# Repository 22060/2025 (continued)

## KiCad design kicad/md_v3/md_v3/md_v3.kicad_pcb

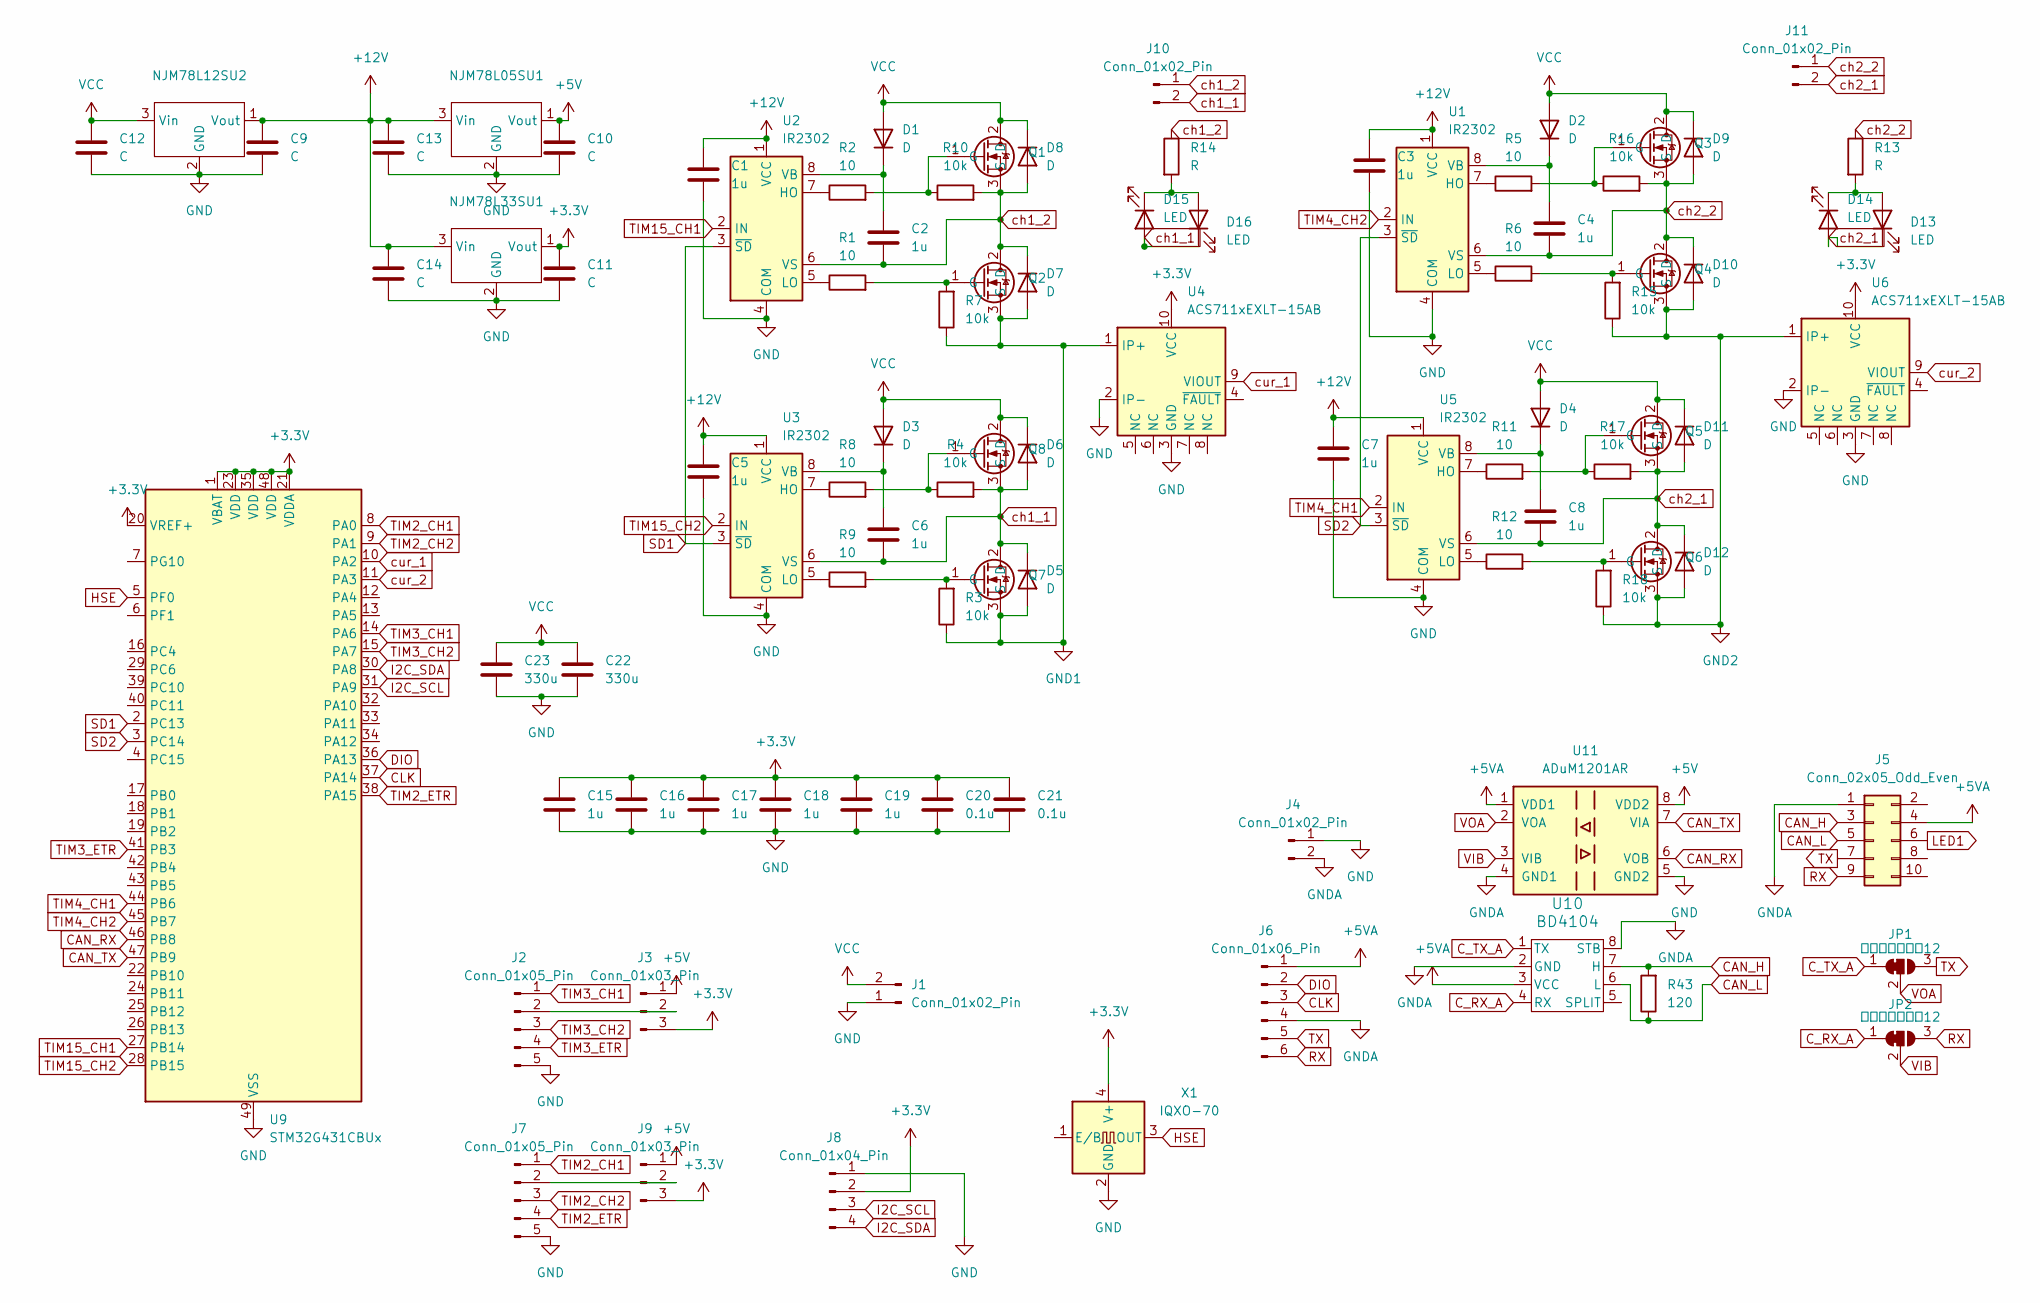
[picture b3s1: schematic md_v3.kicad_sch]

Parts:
C1, C2, C3, C4, C5, C6, C7, C8, C15, C16, C17, C18, C19: 1u; C_0603_1608Metric
C9, C10, C11, C12, C13, C14: C; C_0603_1608Metric
C20, C21: 0.1u; C_0603_1608Metric
C22, C23: 330u; C_Elec_10x10.2
D1, D2, D3, D4: D; D_MicroSMP_AK
D5, D6, D7, D8, D9, D10, D11, D12: D; D_SOD-323_HandSoldering
D13, D14, D15, D16: LED; LED_0603_1608Metric
J1: Conn_01x02_Pin; AMASS_XT30PW-M_1x02_P2.50mm_Horizontal
J2, J7: Conn_01x05_Pin; JST_XH_S5B-XH-A_1x05_P2.50mm_Horizontal
J3, J9: Conn_01x03_Pin; PinSocket_1x03_P2.54mm_Vertical
J4: Conn_01x02_Pin; PinHeader_1x02_P2.54mm_Vertical
J5: Conn_02x05_Odd_Even; PinHeader_2x05_P2.54mm_Horizontal
J6: Conn_01x06_Pin; JST_ZH_B6B-ZR_1x06_P1.50mm_Vertical
J8: Conn_01x04_Pin; PinSocket_1x04_P2.54mm_Vertical
J10, J11: Conn_01x02_Pin; AMASS_XT30PW-F_1x02_P2.50mm_Horizontal
JP1, JP2: ソルダジャンパ12; SolderJumper-3_P1.3mm_Bridged12_Pad1.0x1.5mm
NJM78L05SU1, NJM78L12SU2, NJM78L33SU1: SOT-89-3
Q1, Q2, Q3, Q4, Q5, Q6, Q7, Q8: RD3L07BBG
R1, R2, R5, R6, R8, R9, R11, R12: 10; R_0603_1608Metric_Pad0.98x0.95mm_HandSolder
R3, R4, R7, R10, R15, R16, R17, R18: 10k; R_0603_1608Metric_Pad0.98x0.95mm_HandSolder
R13, R14: R; R_0603_1608Metric_Pad0.98x0.95mm_HandSolder
R43: 120; R_0603_1608Metric_Pad0.98x0.95mm_HandSolder
U1, U2, U3, U5: IR2302; SOIC-8_3.9x4.9mm_P1.27mm
U4, U6: ACS711xEXLT-15AB; Allegro_QFN-12-10-1EP_3x3mm_P0.5mm
U9: STM32G431CBUx; QFN-48-1EP_7x7mm_P0.5mm_EP5.6x5.6mm
U10: BD4104; SOP-J8
U11: ADuM1201AR; SOIC-8_3.9x4.9mm_P1.27mm
X1: IQXO-70; Oscillator_SMD_IQD_IQXO70-4Pin_7.5x5.0mm

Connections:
+3.3V: C11.1, C15.1, C16.1, C17.1, C18.1, C19.1, C20.1, C21.1, J3.3, J8.2, J9.3, NJM78L33SU1.1 (Vout), U4.10 (VCC), U6.10 (VCC), U9.1 (VBAT), U9.20 (VREF+), U9.21 (VDDA), U9.23 (VDD), U9.35 (VDD), U9.48 (VDD), X1.4 (V+)
+5V: C10.1, J3.1, J9.1, NJM78L05SU1.1 (Vout), U11.8 (VDD2)
+5VA: J5.4, J6.1, U10.3 (VCC), U11.1 (VDD1)
+12V: C1.1, C3.1, C5.1, C7.1, C9.1, C13.1, C14.1, NJM78L05SU1.3 (Vin), NJM78L12SU2.1 (Vout), NJM78L33SU1.3 (Vin), U1.1 (VCC), U2.1 (VCC), U3.1 (VCC), U5.1 (VCC)
CAN_H: J5.3, R43.2, U10.7 (H)
CAN_L: J5.5, R43.1, U10.6 (L)
CAN_RX: U9.46 (PB8), U11.6 (VOB)
CAN_TX: U9.47 (PB9), U11.7 (VIA)
CLK: J6.3, U9.37 (PA14)
C_RX_A: JP2.1 (A), U10.4 (RX)
C_TX_A: JP1.1 (A), U10.1 (TX)
DIO: J6.2, U9.36 (PA13)
GND: C1.2, C3.2, C5.2, C7.2, C9.2, C10.2, C11.2, C12.2, C13.2, C14.2, C15.2, C16.2, C17.2, C18.2, C19.2, C20.2, C21.2, C22.2, C23.2, J1.1, J2.5, J4.1, J7.5, J8.1, NJM78L05SU1.2 (GND), NJM78L12SU2.2 (GND), NJM78L33SU1.2 (GND), U1.4 (COM), U2.4 (COM), U3.4 (COM), U4.2 (IP-), U4.3 (GND), U5.4 (COM), U6.2 (IP-), U6.3 (GND), U9.49 (VSS), U11.5 (GND2), X1.2 (GND)
GND1: D5.2 (A), D7.2 (A), Q2.3 (S), Q7.3 (S), R3.1, R7.1, U4.1 (IP+)
GND2: D10.2 (A), D12.2 (A), Q4.3 (S), Q6.3 (S), R15.1, R18.1, U6.1 (IP+)
GNDA: J4.2, J5.1, J6.4, U10.2 (GND), U10.8 (STB), U11.4 (GND1)
HSE: U9.5 (PF0), X1.3 (OUT)
I2C_SCL: J8.3, U9.31 (PA9)
I2C_SDA: J8.4, U9.30 (PA8)
LED1: J5.6
unnamed: C2.1, D1.1 (K), U2.8 (VB)
unnamed: C4.1, D2.1 (K), U1.8 (VB)
unnamed: C6.1, D3.1 (K), U3.8 (VB)
unnamed: C8.1, D4.1 (K), U5.8 (VB)
unnamed: D13.2 (A), D14.1 (K), R13.2
unnamed: D15.1 (K), D16.2 (A), R14.2
unnamed: J2.2, J3.2
unnamed: J7.2, J9.2
unnamed: Q1.1 (G), R2.2, R10.1
unnamed: Q2.1 (G), R1.2, R7.2
unnamed: Q3.1 (G), R5.2, R16.1
unnamed: Q4.1 (G), R6.2, R15.2
unnamed: Q5.1 (G), R11.2, R17.1
unnamed: Q6.1 (G), R12.2, R18.2
unnamed: Q7.1 (G), R3.2, R9.2
unnamed: Q8.1 (G), R4.1, R8.2
unnamed: R5.1, U1.7 (HO)
unnamed: R6.1, U1.5 (LO)
unnamed: R2.1, U2.7 (HO)
unnamed: R1.1, U2.5 (LO)
unnamed: R8.1, U3.7 (HO)
unnamed: R9.1, U3.5 (LO)
unnamed: R11.1, U5.7 (HO)
unnamed: R12.1, U5.5 (LO)
RX: J5.9, J6.6, JP2.3 (B)
SD1: U2.3 (~SD), U3.3 (~SD), U9.2 (PC13)
SD2: U1.3 (~SD), U5.3 (~SD), U9.3 (PC14)
TIM2_CH1: J7.1, U9.8 (PA0)
TIM2_CH2: J7.3, U9.9 (PA1)
TIM2_ETR: J7.4, U9.38 (PA15)
TIM3_CH1: J2.1, U9.14 (PA6)
TIM3_CH2: J2.3, U9.15 (PA7)
TIM3_ETR: J2.4, U9.41 (PB3)
TIM4_CH1: U5.2 (IN), U9.44 (PB6)
TIM4_CH2: U1.2 (IN), U9.45 (PB7)
TIM15_CH1: U2.2 (IN), U9.27 (PB14)
TIM15_CH2: U3.2 (IN), U9.28 (PB15)
TX: J5.7, J6.5, JP1.3 (B)
VCC: C12.1, C22.1, C23.1, D1.2 (A), D2.2 (A), D3.2 (A), D4.2 (A), D6.1 (K), D8.1 (K), D9.1 (K), D11.1 (K), J1.2, NJM78L12SU2.3 (Vin), Q1.2 (D), Q3.2 (D), Q5.2 (D), Q8.2 (D)
VIB: JP2.2 (C), U11.3 (VIB)
VOA: JP1.2 (C), U11.2 (VOA)
ch1_1: C6.2, D5.1 (K), D6.2 (A), D15.2 (A), D16.1 (K), J10.2, Q7.2 (D), Q8.3 (S), R4.2, U3.6 (VS)
ch1_2: C2.2, D7.1 (K), D8.2 (A), J10.1, Q1.3 (S), Q2.2 (D), R10.2, R14.1, U2.6 (VS)
ch2_1: C8.2, D11.2 (A), D12.1 (K), D13.1 (K), D14.2 (A), J11.2, Q5.3 (S), Q6.2 (D), R17.2, U5.6 (VS)
ch2_2: C4.2, D9.2 (A), D10.1 (K), J11.1, Q3.3 (S), Q4.2 (D), R13.1, R16.2, U1.6 (VS)
cur_1: U4.9 (VIOUT), U9.10 (PA2)
cur_2: U6.9 (VIOUT), U9.11 (PA3)

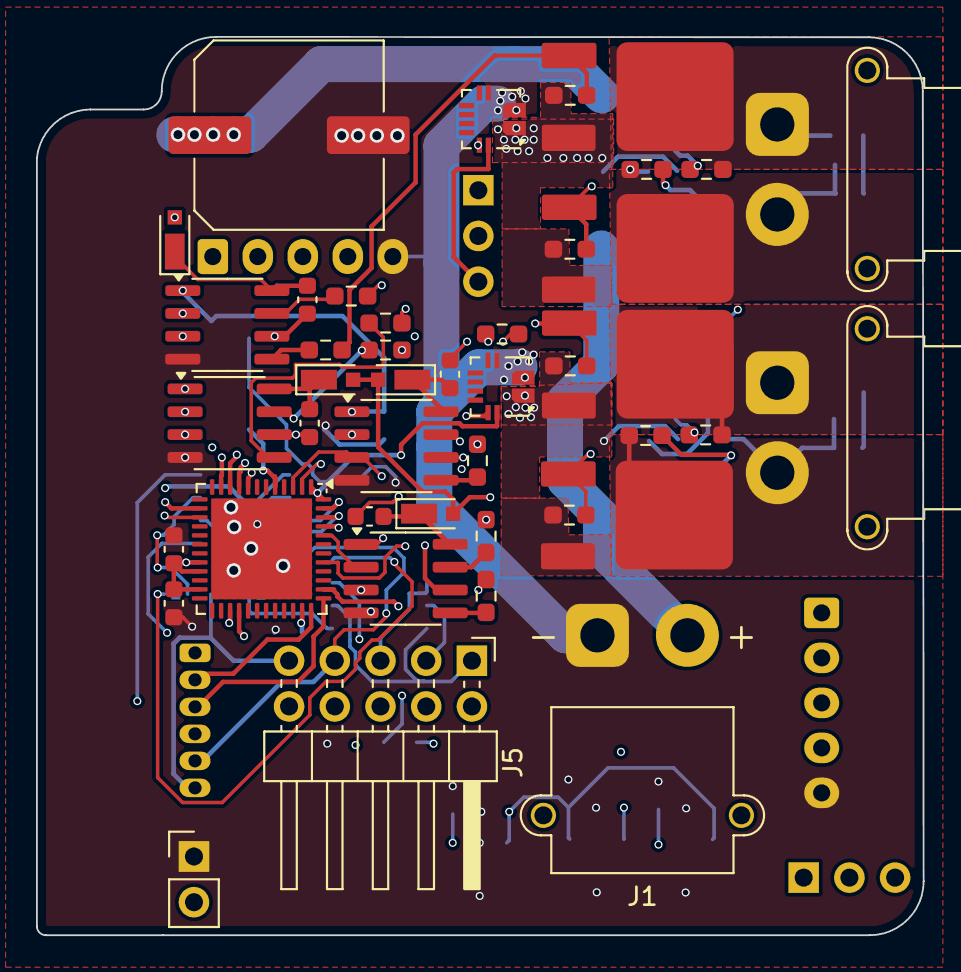
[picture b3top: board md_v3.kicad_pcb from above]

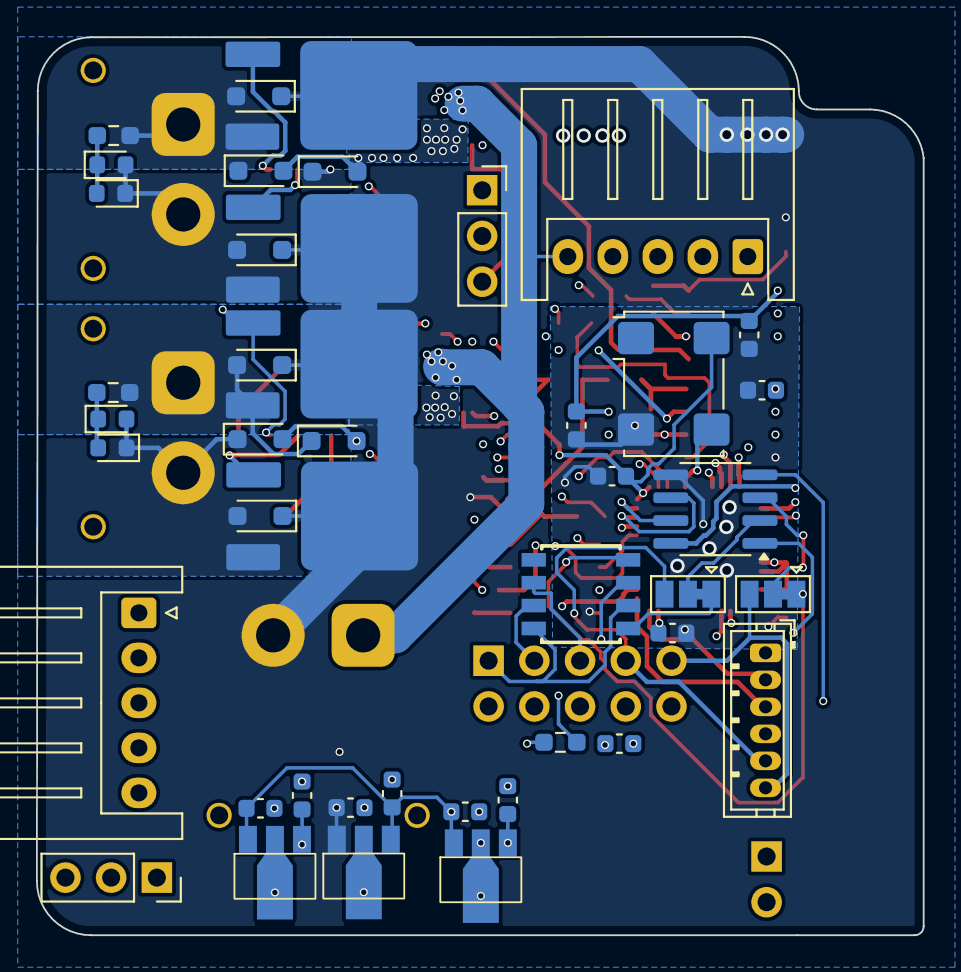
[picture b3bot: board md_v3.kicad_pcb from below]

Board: 4 copper layers, 49.3 x 49.9 mm, 87 parts (44 on the bottom side), 64 nets.

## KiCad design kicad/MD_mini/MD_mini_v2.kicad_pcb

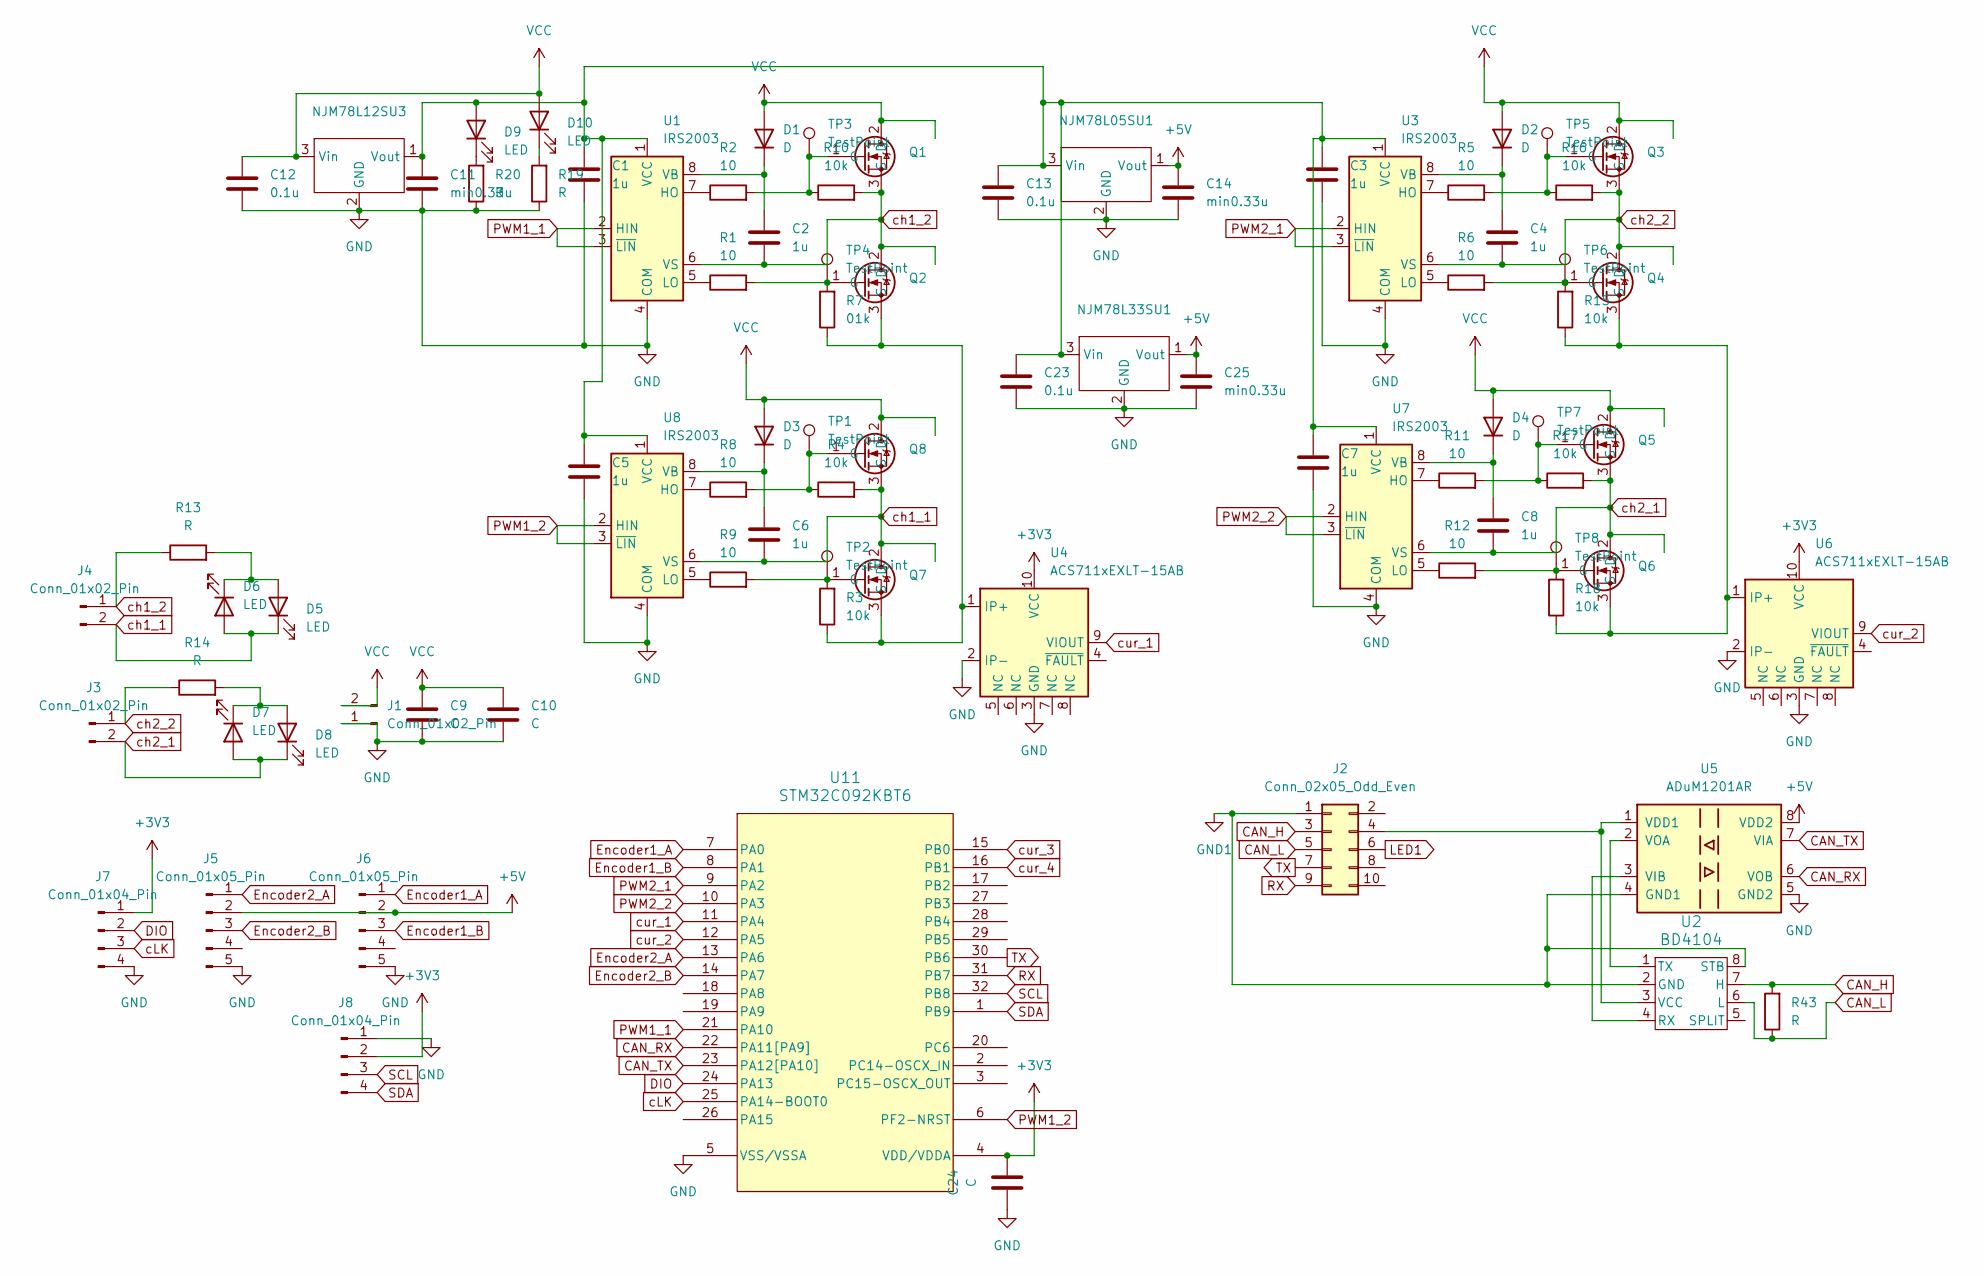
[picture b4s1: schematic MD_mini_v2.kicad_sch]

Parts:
C1, C2, C3, C4, C5, C6, C7, C8: 1u; C_0603_1608Metric
C9, C10: C; C_Elec_10x10.2
C11, C14, C25: min0.33u; C_0603_1608Metric
C12, C13, C23: 0.1u; C_0603_1608Metric
C24: C; C_0603_1608Metric
D1, D2, D3, D4: D; D_MicroSMP_AK
D5, D6, D7, D8, D9, D10: LED; LED_0603_1608Metric_Pad1.05x0.95mm_HandSolder
J1: Conn_01x02_Pin; AMASS_XT30PW-M_1x02_P2.50mm_Horizontal
J2: Conn_02x05_Odd_Even; PinHeader_2x05_P2.54mm_Horizontal
J3, J4: Conn_01x02_Pin; AMASS_XT30PW-F_1x02_P2.50mm_Horizontal
J5, J6: Conn_01x05_Pin; PinHeader_1x05_P2.54mm_Horizontal
J7, J8: Conn_01x04_Pin; PinSocket_1x04_P2.54mm_Vertical
NJM78L05SU1, NJM78L12SU3, NJM78L33SU1: SOT-89-3
Q1, Q2, Q3, Q4, Q5, Q6, Q7, Q8: RD3L07BBG
R1, R2, R5, R6, R8, R9, R11, R12: 10; R_0603_1608Metric_Pad0.98x0.95mm_HandSolder
R3, R4, R10, R15, R16, R17, R18: 10k; R_0603_1608Metric_Pad0.98x0.95mm_HandSolder
R7: 01k; R_0603_1608Metric_Pad0.98x0.95mm_HandSolder
R13, R14, R19, R20, R43: R; R_0603_1608Metric_Pad0.98x0.95mm_HandSolder
TP1, TP2, TP3, TP4, TP5, TP6, TP7, TP8: TestPoint
U1, U3, U7, U8: IRS2003; SOIC-8_3.9x4.9mm_P1.27mm
U2: BD4104; SOP-J8
U4, U6: ACS711xEXLT-15AB; Allegro_QFN-12-10-1EP_3x3mm_P0.5mm
U5: ADuM1201AR; SOIC-8_3.9x4.9mm_P1.27mm
U11: STM32C092KBT6; LQFP-32_7x7mm_P0.8mm

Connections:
+3V3: C24.1, J7.1, J8.2, U4.10 (VCC), U6.10 (VCC), U11.4 (VDD/VDDA)
+5V: C14.1, C25.1, J5.2, J6.2, NJM78L05SU1.1 (Vout), NJM78L33SU1.1 (Vout), U5.8 (VDD2)
CAN_H: J2.3, R43.2, U2.7 (H)
CAN_L: J2.5, R43.1, U2.6 (L)
CAN_RX: U5.6 (VOB), U11.22 (PA11[PA9])
CAN_TX: U5.7 (VIA), U11.23 (PA12[PA10])
DIO: J7.2, U11.24 (PA13)
Encoder1_A: J6.1, U11.7 (PA0)
Encoder1_B: J6.3, U11.8 (PA1)
Encoder2_A: J5.1, U11.13 (PA6)
Encoder2_B: J5.3, U11.14 (PA7)
GND: C1.2, C3.2, C5.2, C7.2, C9.2, C10.2, C11.2, C12.2, C13.2, C14.2, C23.2, C24.2, C25.2, J1.1, J5.5, J6.5, J7.4, J8.1, NJM78L05SU1.2 (GND), NJM78L12SU3.2 (GND), NJM78L33SU1.2 (GND), R19.1, R20.1, U1.4 (COM), U3.4 (COM), U4.2 (IP-), U4.3 (GND), U5.5 (GND2), U6.2 (IP-), U6.3 (GND), U7.4 (COM), U8.4 (COM), U11.5 (VSS/VSSA)
GND1: J2.1, U2.2 (GND), U2.8 (STB), U5.4 (GND1)
LED1: J2.6
unnamed: C2.1, D1.1 (K), U1.8 (VB)
unnamed: C4.1, D2.1 (K), U3.8 (VB)
unnamed: C6.1, D3.1 (K), U8.8 (VB)
unnamed: C8.1, D4.1 (K), U7.8 (VB)
unnamed: D5.2 (A), D6.1 (K), R13.2
unnamed: D7.1 (K), D8.2 (A), R14.2
unnamed: C1.1, C3.1, C5.1, C7.1, C11.1, C13.1, C23.1, D9.2 (A), NJM78L05SU1.3 (Vin), NJM78L12SU3.1 (Vout), NJM78L33SU1.3 (Vin), U1.1 (VCC), U3.1 (VCC), U7.1 (VCC), U8.1 (VCC)
unnamed: D9.1 (K), R20.2
unnamed: D10.1 (K), R19.2
unnamed: J2.4, U2.3 (VCC), U5.1 (VDD1)
unnamed: Q1.1 (G), R2.2, R10.1, TP3.1
unnamed: Q2.1 (G), R1.2, R7.2, TP4.1
unnamed: Q2.3 (S), Q7.3 (S), R3.1, R7.1, U4.1 (IP+)
unnamed: Q3.1 (G), R5.2, R16.1, TP5.1
unnamed: Q4.1 (G), R6.2, R15.2, TP6.1
unnamed: Q4.3 (S), Q6.3 (S), R15.1, R18.1, U6.1 (IP+)
unnamed: Q5.1 (G), R11.2, R17.1, TP7.1
unnamed: Q6.1 (G), R12.2, R18.2, TP8.1
unnamed: Q7.1 (G), R3.2, R9.2, TP2.1
unnamed: Q8.1 (G), R4.1, R8.2, TP1.1
unnamed: R2.1, U1.7 (HO)
unnamed: R1.1, U1.5 (LO)
unnamed: U2.4 (RX), U5.3 (VIB)
unnamed: U2.1 (TX), U5.2 (VOA)
unnamed: R5.1, U3.7 (HO)
unnamed: R6.1, U3.5 (LO)
unnamed: R11.1, U7.7 (HO)
unnamed: R12.1, U7.5 (LO)
unnamed: R8.1, U8.7 (HO)
unnamed: R9.1, U8.5 (LO)
PWM1_1: U1.2 (HIN), U1.3 (~LIN), U11.21 (PA10)
PWM1_2: U8.2 (HIN), U8.3 (~LIN), U11.6 (PF2-NRST)
PWM2_1: U3.2 (HIN), U3.3 (~LIN), U11.9 (PA2)
PWM2_2: U7.2 (HIN), U7.3 (~LIN), U11.10 (PA3)
RX: J2.9, U11.31 (PB7)
SCL: J8.3, U11.32 (PB8)
SDA: J8.4, U11.1 (PB9)
TX: J2.7, U11.30 (PB6)
VCC: C9.1, C10.1, C12.1, D1.2 (A), D2.2 (A), D3.2 (A), D4.2 (A), D10.2 (A), J1.2, NJM78L12SU3.3 (Vin), Q1.2 (D), Q3.2 (D), Q5.2 (D), Q8.2 (D)
cLK: J7.3, U11.25 (PA14-BOOT0)
ch1_1: C6.2, D5.1 (K), D6.2 (A), J4.2, Q7.2 (D), Q8.3 (S), R4.2, U8.6 (VS)
ch1_2: C2.2, J4.1, Q1.3 (S), Q2.2 (D), R10.2, R13.1, U1.6 (VS)
ch2_1: C8.2, D7.2 (A), D8.1 (K), J3.2, Q5.3 (S), Q6.2 (D), R17.2, U7.6 (VS)
ch2_2: C4.2, J3.1, Q3.3 (S), Q4.2 (D), R14.1, R16.2, U3.6 (VS)
cur_1: U4.9 (VIOUT), U11.11 (PA4)
cur_2: U6.9 (VIOUT), U11.12 (PA5)
cur_3: U11.15 (PB0)
cur_4: U11.16 (PB1)

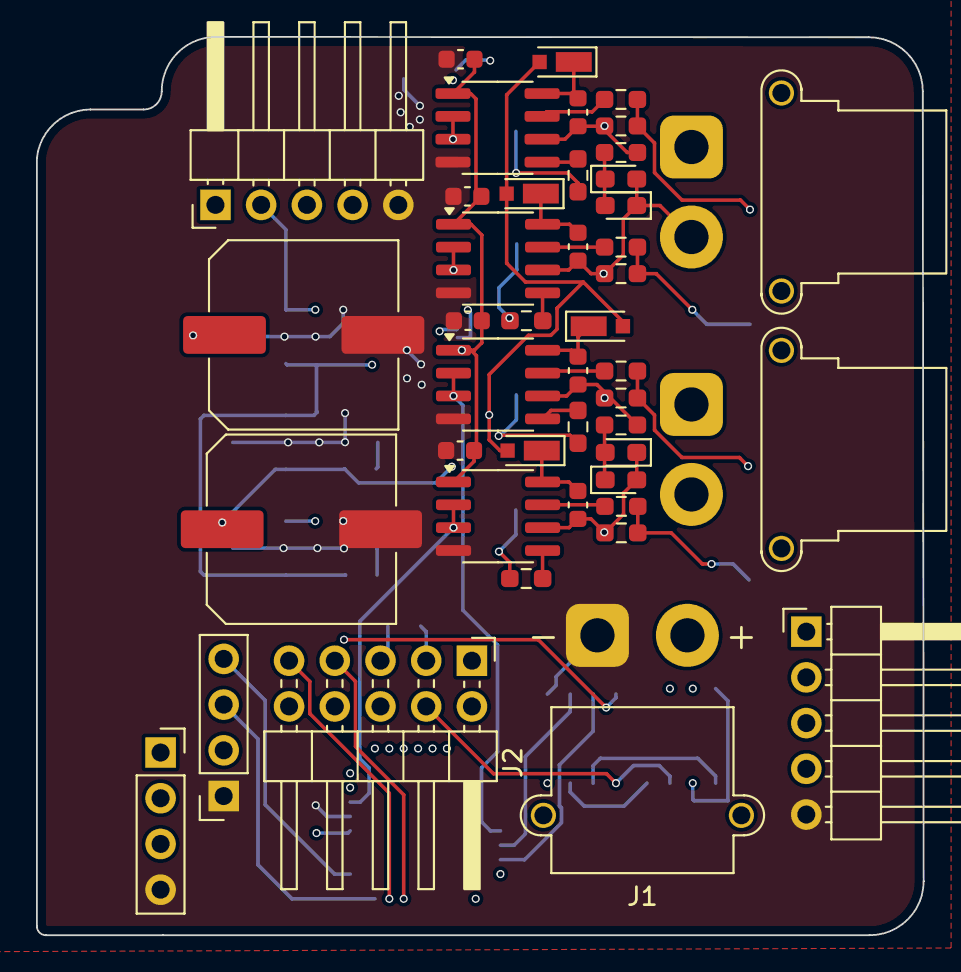
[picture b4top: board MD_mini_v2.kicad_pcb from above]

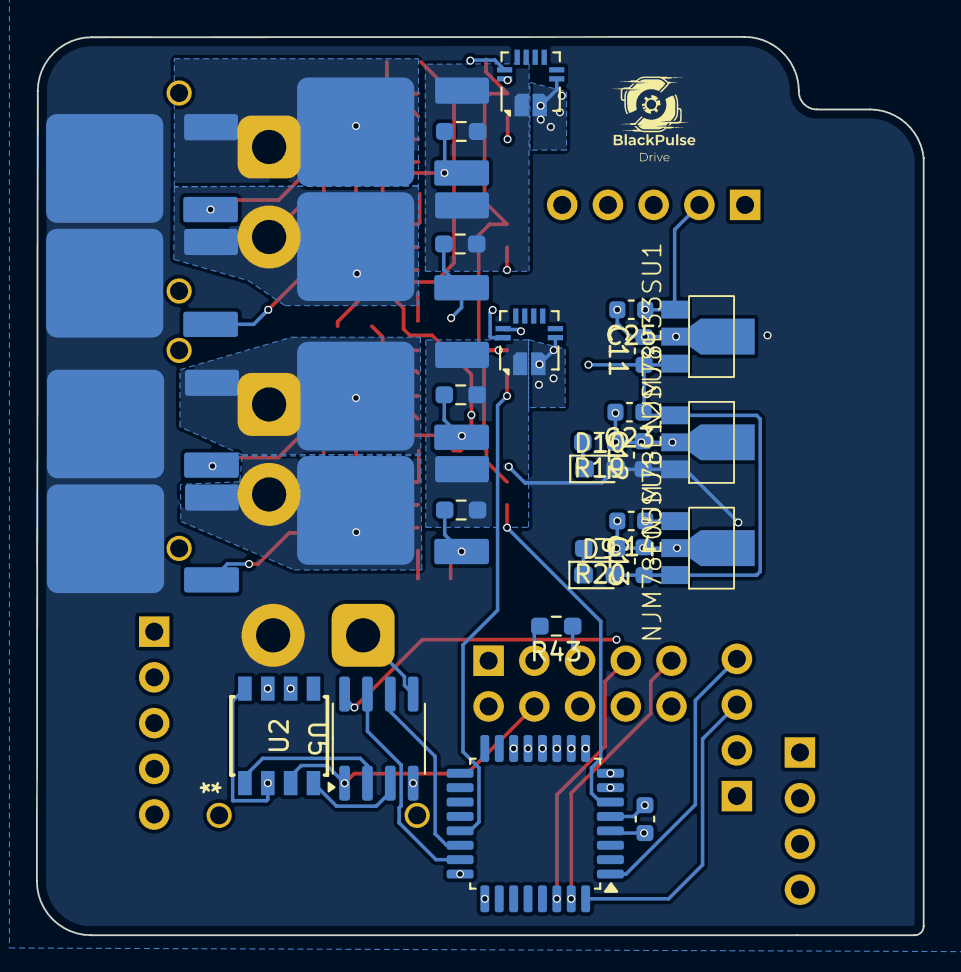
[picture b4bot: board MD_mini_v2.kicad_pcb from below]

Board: 4 copper layers, 49.3 x 49.9 mm, 76 parts (32 on the bottom side), 59 nets.

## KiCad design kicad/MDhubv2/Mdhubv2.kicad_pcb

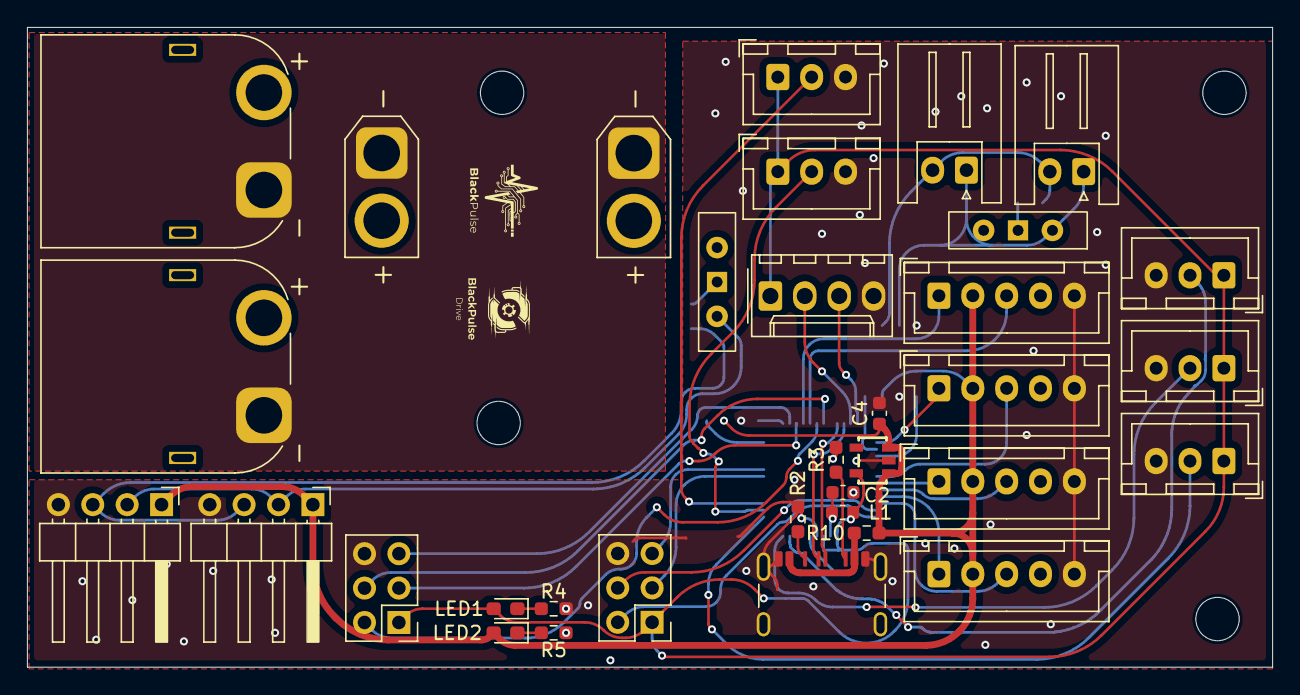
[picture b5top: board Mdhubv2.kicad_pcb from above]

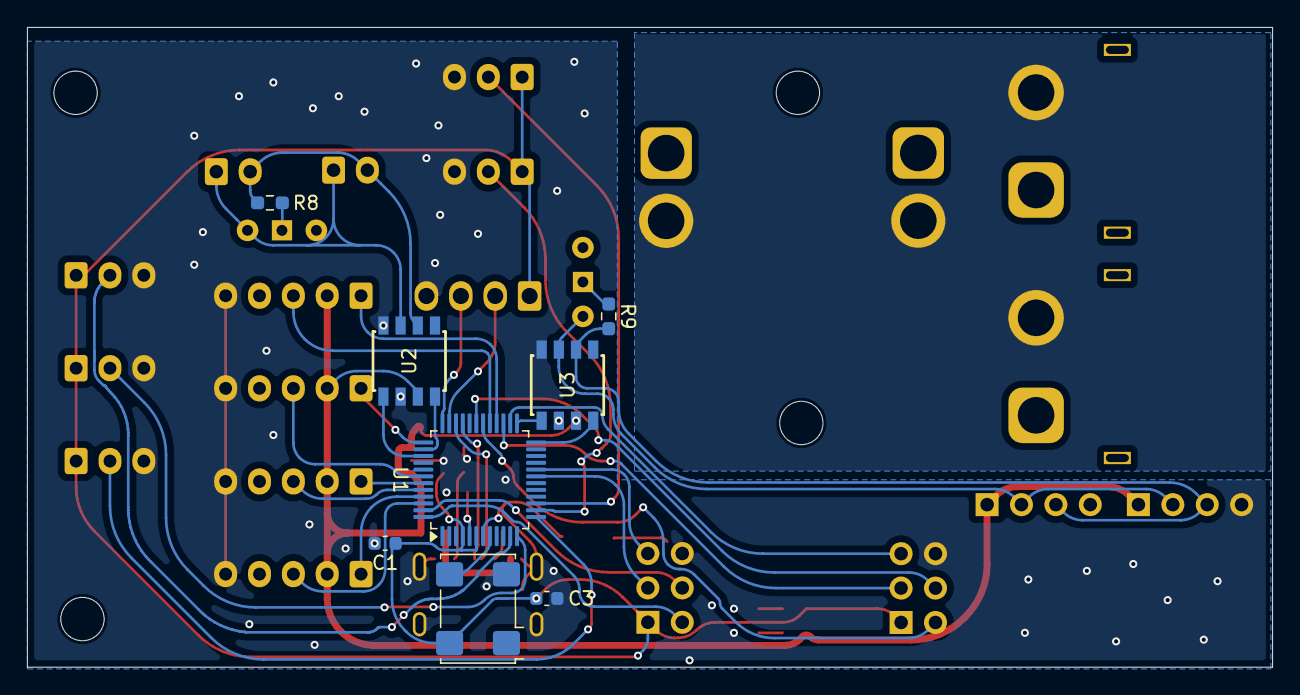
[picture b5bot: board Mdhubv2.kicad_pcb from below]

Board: 2 copper layers, 91.9 x 47.2 mm, 46 parts (8 on the bottom side), 47 nets.

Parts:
C1, C2, C3: 0.1u; C_0603_1608Metric
C4: 10u(DFP; C_0603_1608Metric
DCDC1: BU33TD3WG; SSOP5
H1, H2, H3, H4: MountingHole; MountingHole_3.2mm_M3
J1: USB_C_Receptacle_USB2.0_14P; USB_C_Receptacle_aitendo
J2: Conn_01x04_Pin; Molex_KK-254_AE-6410-04A_1x04_P2.54mm_Vertical
J3, J4, J5, J6: Conn_01x05_Pin; JST_XH_B5B-XH-A_1x05_P2.50mm_Vertical
J7, J8: Conn_02x03_Counter_Clockwise; PinHeader_2x03_P2.54mm_Vertical
J12, J20: Conn_01x04_Pin; PinHeader_1x04_P2.54mm_Horizontal
J14, J15: Conn_01x02_Pin; JST_XH_S2B-XH-A_1x02_P2.50mm_Horizontal
J19, J21: Conn_01x02_Pin; AMASS_XT30U-F_1x02_P5.0mm_Vertical
J22, J25: Conn_01x02_Pin; AMASS_XT60PW-M_1x02_P7.20mm_Horizontal
J26, J27, J28, J29, J30: Conn_01x03_Pin; JST_XH_B3B-XH-A_1x03_P2.50mm_Vertical
L1: L; L_0603_1608Metric
LED1, LED2: LED; LED_0603_1608Metric_Pad1.05x0.95mm_HandSolder
R2, R3: 5.1k; R_0603_1608Metric_Pad0.98x0.95mm_HandSolder
R4, R5: 165; R_0603_1608Metric_Pad0.98x0.95mm_HandSolder
R8, R9: R; R_0603_1608Metric_Pad0.98x0.95mm_HandSolder
R10: fuse; R_0603_1608Metric_Pad0.98x0.95mm_HandSolder
SW1, SW2: SW_Wuerth_450301014042; SW_Slide-03_Wuerth-WS-SLTV_10x2.5x6.4_P2.54mm
U1: STM32G0B1CBTx; LQFP-48_7x7mm_P0.5mm
U2, U3: SOP-J8
X1: IQXO-70; Oscillator_SMD_IQD_IQXO70-4Pin_7.5x5.0mm

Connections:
+3V3: C1.1, C3.1, DCDC1.5 (VOUT), J2.1, J7.1, J8.1, J26.1, J27.1, J28.1, J29.1, J30.1, L1.2, LED1.2 (A), U1.4 (VBAT), U1.6 (VDD), X1.4 (V+)
ADC0: J28.2, U1.11 (PA0)
ADC1: J29.2, U1.12 (PA1)
ADC2: J30.2, U1.13 (PA2)
ADC3: J27.2, U1.14 (PA3)
ADC4: J26.2, U1.15 (PA4)
CAN1_RX: U1.38 (PD0), U2.4 (RXD)
CAN1_TX: U1.39 (PD1), U2.1 (TXD)
CAN2_RX: U1.24 (PB12), U3.4 (RXD)
CAN2_TX: U1.25 (PB13), U3.1 (TXD)
CAN_H: J14.1, J15.1, SW1.2 (C), U2.7 (CANH)
CAN_H2: J12.2, J20.2, SW2.2 (C), U3.7 (CANH)
CAN_L: J14.2, J15.2, R8.2, U2.6 (CANL)
CAN_L2: J12.3, J20.3, R9.2, U3.6 (CANL)
CLK: J2.3, U1.36 (PA14)
DIO: J2.2, U1.35 (PA13)
GND: C1.2, C2.2, C3.2, C4.2, DCDC1.2 (GND), J1.A1 (GND), J1.A12 (GND), J1.B1 (GND), J1.B12 (GND), J1.S1 (SHIELD), J2.4, J3.5, J4.5, J5.5, J6.5, J7.6, J8.6, J12.4, J20.4, J26.3, J27.3, J28.3, J29.3, J30.3, R2.1, R3.2, R4.2, R5.2, U1.7 (VSS), U2.2 (GND), U2.8 (STB), U3.2 (GND), U3.8 (STB), X1.2 (GND)
GND1: J19.1, J21.1, J22.1, J25.1
unnamed: J1.A5 (CC1), R2.2
unnamed: J1.B5 (CC2), R3.1
unnamed: J1.A4 (VBUS), J1.A9 (VBUS), J1.B4 (VBUS), J1.B9 (VBUS), R10.1
unnamed: LED1.1 (K), R4.1
unnamed: LED2.1 (K), R5.1
unnamed: R8.1, SW1.1 (B)
unnamed: R9.1, SW2.1 (B)
PA8: J3.1, U1.28 (PA8)
PA9: J3.3, U1.29 (PA9/UCPD1_DBCC1)
PA11: J1.A7 (D-), U1.33 (PA9/PA11)
PA12: J1.A6 (D+), U1.34 (PA10/PA12)
PA15: J4.1, U1.37 (PA15)
PB0: J8.3, U1.19 (PB0)
PB1: J8.5, U1.20 (PB1)
PB3: J4.3, U1.42 (PB3)
PB4: J5.1, U1.43 (PB4)
PB5: J5.3, U1.44 (PB5)
PB6: J6.1, U1.45 (PB6)
PB7: J6.3, U1.46 (PB7)
PB8: J8.4, U1.47 (PB8)
PB9: J8.2, U1.48 (PB9)
PB14: J7.5, U1.26 (PB14)
PB15: J7.3, U1.27 (PB15)
PC6: J7.2, U1.30 (PC6)
PC7: J7.4, U1.31 (PC7)
PF0: U1.8 (PF0), X1.3 (OUT)
VBUS: C4.1, DCDC1.1 (VIN), DCDC1.3 (STBY), J3.2, J4.2, J5.2, J6.2, J12.1, J20.1, LED2.2 (A), R10.2, U2.3 (VCC), U3.3 (VCC)
VREF: C2.1, L1.1, U1.5 (VREF+)
VS: J19.2, J21.2, J22.2, J25.2
